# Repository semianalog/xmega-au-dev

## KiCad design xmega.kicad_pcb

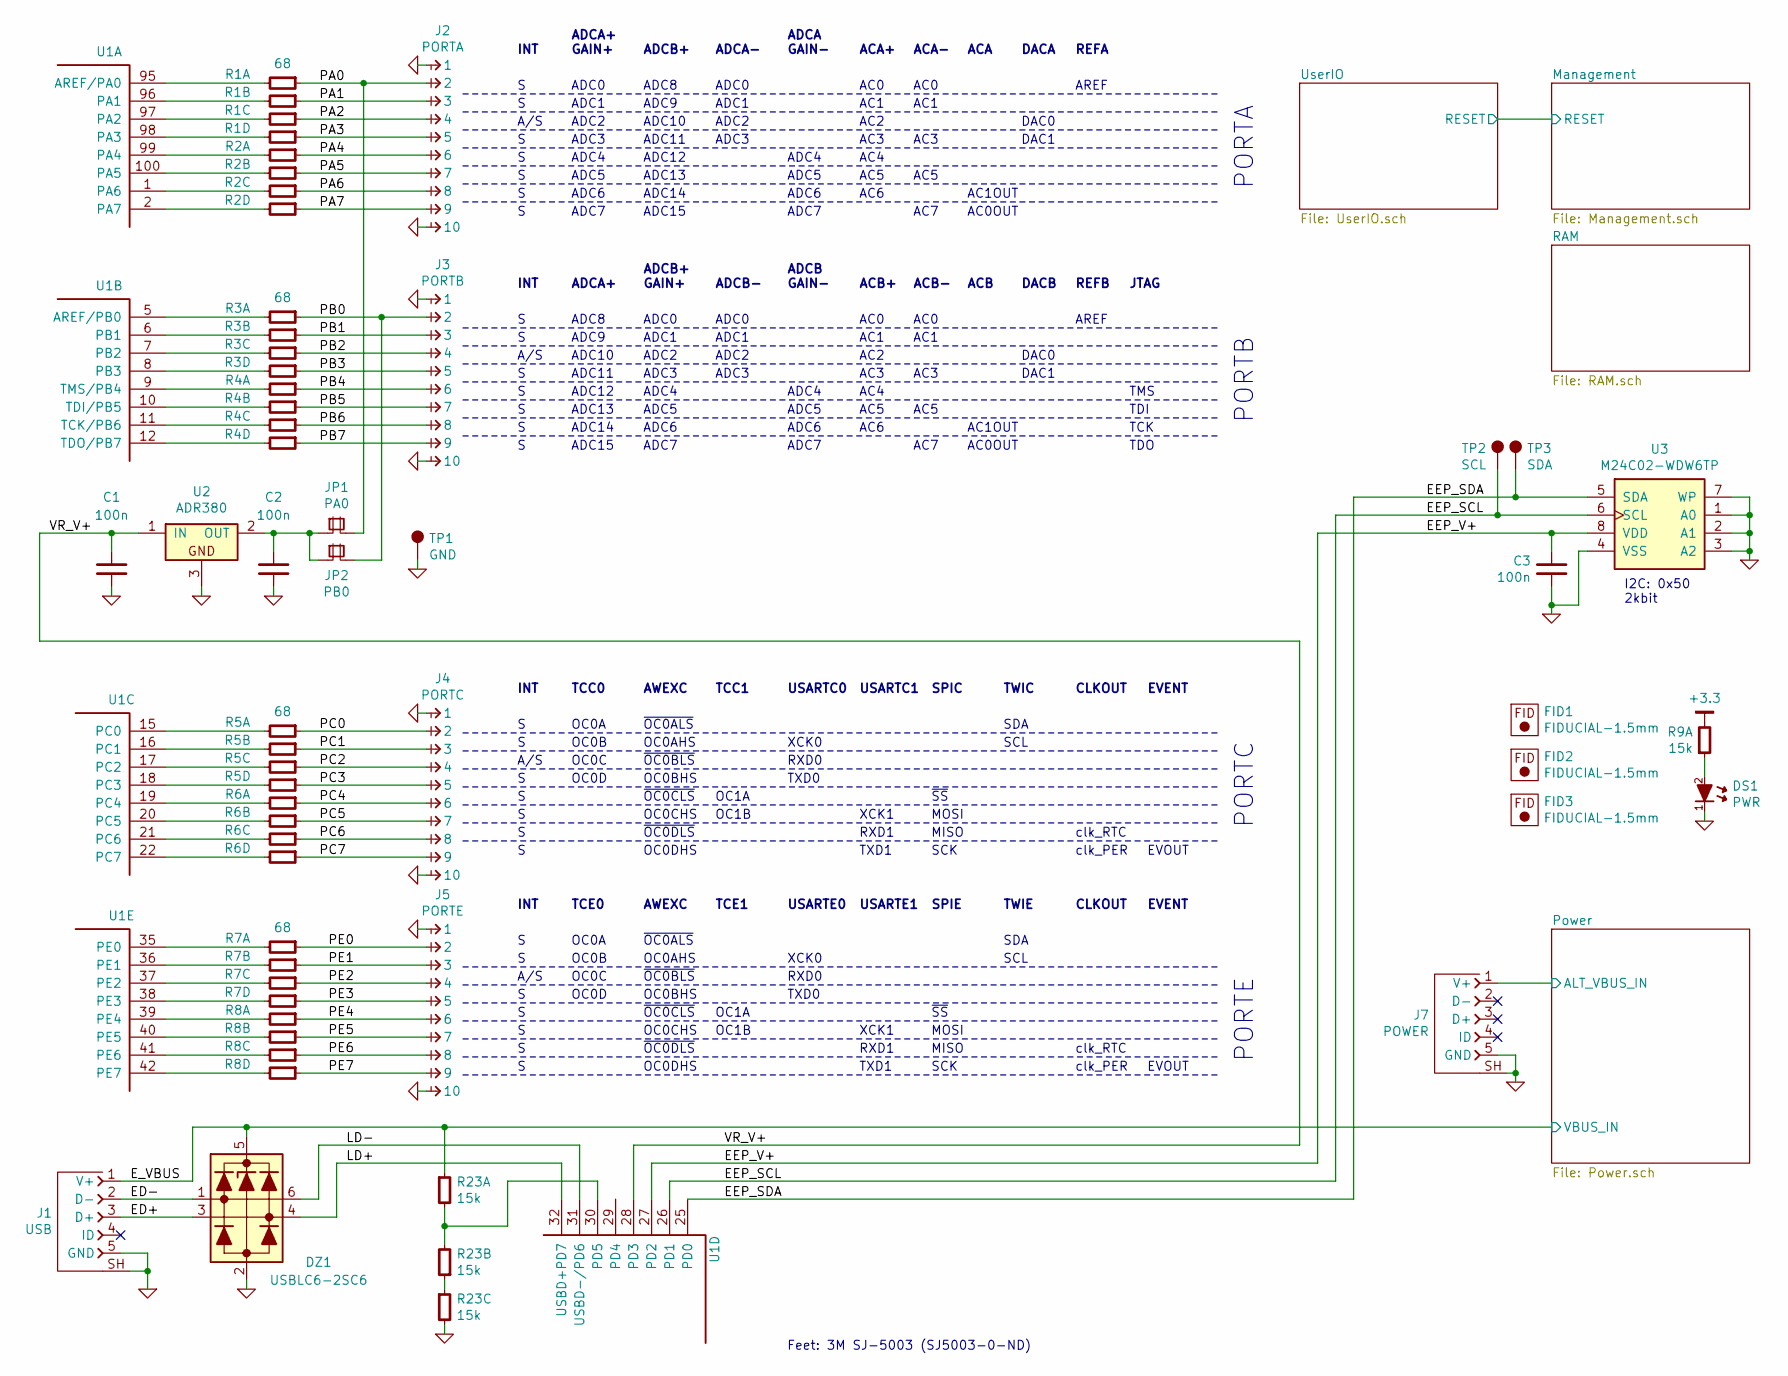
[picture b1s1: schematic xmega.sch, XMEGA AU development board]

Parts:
C1, C2, C3: 100n; CAPC1005X55
DS1: PWR; LED-0603
DZ1: USBLC6-2SC6; SOT-23-6
FID1, FID2, FID3: FIDUCIAL-1.5mm
J1: USB; CONN-10118194-0001LF-FCI
J2: PORTA; CONN-100MIL-M-1x10
J3: PORTB; CONN-100MIL-M-1x10
J4: PORTC; CONN-100MIL-M-1x10
J5: PORTE; CONN-100MIL-M-1x10
J7: POWER; CONN-10118194-0001LF-FCI
JP1: PA0; CONN-100MIL-M-1x2
JP2: PB0; CONN-100MIL-M-1x2
R1, R2, R3, R4, R5, R6, R7, R8: 68; RESCAXE80P160X320X70-8
R9, R23: 15k; RESCAXE80P160X320X70-8
TP1: GND; TESTPOINT-KEYSTONE-5018
TP2: SCL; TEST-SMD-SMALL
TP3: SDA; TEST-SMD-SMALL
U1: ATXMEGA128A1U-AU; QFP50P1600X1600X120-100
U2: ADR380; SOT-23
U3: M24C02-WDW6TP; SOP65P640X110-8

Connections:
+3.3: R9.8; also elsewhere on the board
/ED+: DZ1.3, J1.3 (D+)
/ED-: DZ1.1, J1.2 (D-)
/EEP_SCL: TP2.1, U1.26 (PD1), U3.6 (SCL)
/EEP_SDA: TP3.1, U1.25 (PD0), U3.5 (SDA)
/EEP_V+: C3.1, U1.27 (PD2), U3.8 (VDD)
/E_VBUS: DZ1.5, J1.1 (V+), R23.1; also elsewhere on the board
/LD+: DZ1.4, U1.32 (USBD+PD7)
/LD-: DZ1.6, U1.31 (USBD-/PD6)
/PA0: J2.2, JP1.2, R1.1
/PA1: J2.3, R1.2
/PA2: J2.4, R1.3
/PA3: J2.5, R1.4
/PA4: J2.6, R2.1
/PA5: J2.7, R2.2
/PA6: J2.8, R2.3
/PA7: J2.9, R2.4
/PB0: J3.2, JP2.2, R3.1
/PB1: J3.3, R3.2
/PB2: J3.4, R3.3
/PB3: J3.5, R3.4
/PB4: J3.6, R4.1
/PB5: J3.7, R4.2
/PB6: J3.8, R4.3
/PB7: J3.9, R4.4
/PC0: J4.2, R5.1
/PC1: J4.3, R5.2
/PC2: J4.4, R5.3
/PC3: J4.5, R5.4
/PC4: J4.6, R6.1
/PC5: J4.7, R6.2
/PC6: J4.8, R6.3
/PC7: J4.9, R6.4
/PE0: J5.2, R7.1
/PE1: J5.3, R7.2
/PE2: J5.4, R7.3
/PE3: J5.5, R7.4
/PE4: J5.6, R8.1
/PE5: J5.7, R8.2
/PE6: J5.8, R8.3
/PE7: J5.9, R8.4
/Power/ALT_VBUS_IN: J7.1 (V+); also elsewhere on the board
/VR_V+: C1.1, U1.28 (PD3), U2.1 (IN)
GND: C1.2, C2.2, C3.2, DS1.1 (K), DZ1.2, J1.5 (GND), J1.SH (SHIELD), J2.1, J2.10, J3.1, J3.10, J4.1, J4.10, J5.1, J5.10, J7.5 (GND), J7.SH (SHIELD), R23.6, TP1.1, U2.3, U3.1 (A0), U3.2 (A1), U3.3 (A2), U3.4 (VSS), U3.7 (WP); also elsewhere on the board
unnamed: C2.1, JP1.1, JP2.1, U2.2 (OUT)
unnamed: DS1.2 (A), R9.1
unnamed: R1.5, U1.98 (PA3)
unnamed: R1.6, U1.97 (PA2)
unnamed: R1.7, U1.96 (PA1)
unnamed: R1.8, U1.95 (AREF/PA0)
unnamed: R2.5, U1.2 (PA7)
unnamed: R2.6, U1.1 (PA6)
unnamed: R2.7, U1.100 (PA5)
unnamed: R2.8, U1.99 (PA4)
unnamed: R3.5, U1.8 (PB3)
unnamed: R3.6, U1.7 (PB2)
unnamed: R3.7, U1.6 (PB1)
unnamed: R3.8, U1.5 (AREF/PB0)
unnamed: R4.5, U1.12 (TDO/PB7)
unnamed: R4.6, U1.11 (TCK/PB6)
unnamed: R4.7, U1.10 (TDI/PB5)
unnamed: R4.8, U1.9 (TMS/PB4)
unnamed: R5.5, U1.18 (PC3)
unnamed: R5.6, U1.17 (PC2)
unnamed: R5.7, U1.16 (PC1)
unnamed: R5.8, U1.15 (PC0)
unnamed: R6.5, U1.22 (PC7)
unnamed: R6.6, U1.21 (PC6)
unnamed: R6.7, U1.20 (PC5)
unnamed: R6.8, U1.19 (PC4)
unnamed: R7.5, U1.38 (PE3)
unnamed: R7.6, U1.37 (PE2)
unnamed: R7.7, U1.36 (PE1)
unnamed: R7.8, U1.35 (PE0)
unnamed: R8.5, U1.42 (PE7)
unnamed: R8.6, U1.41 (PE6)
unnamed: R8.7, U1.40 (PE5)
unnamed: R8.8, U1.39 (PE4)
unnamed: R23.2, R23.3
unnamed: R23.7, R23.8, U1.30 (PD5)

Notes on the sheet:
I2C: 0x50 2kbit
Feet: 3M SJ-5003 (SJ5003-0-ND)
INT
A/S
TCC0
AWEXC
TCC1
USARTC0
USARTC1
SPIC
TWIC
CLKOUT
EVENT
OC0A
OC0B
OC0C
OC0D
~OC0ALS
OC0AHS
~OC0BLS
OC0BHS
~OC0CLS
OC0CHS
~OC0DLS
OC0DHS
OC1A
OC1B
XCK0
RXD0
TXD0
XCK1
RXD1
TXD1
SDA
SCL
~SS
MOSI
MISO
SCK
clk_RTC

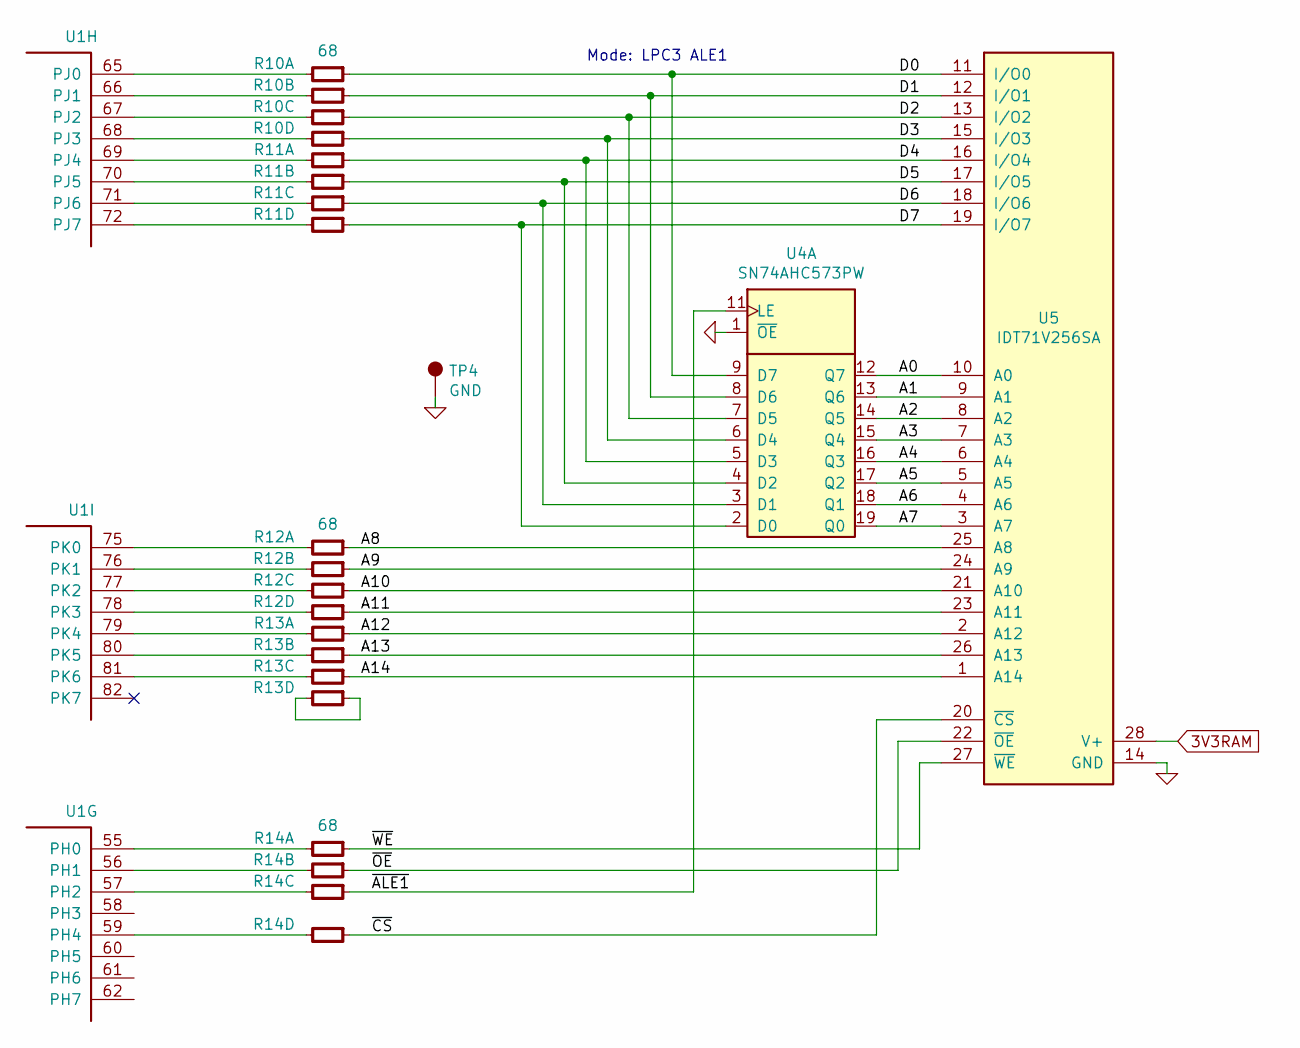
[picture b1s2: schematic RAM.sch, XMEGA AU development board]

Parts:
R10, R11, R12, R13, R14: 68; RESCAXE80P160X320X70-8
TP4: GND; TESTPOINT-KEYSTONE-5018
U1: ATXMEGA128A1U-AU; QFP50P1600X1600X120-100
U4: SN74AHC573PW; SOP65P640X110-20
U5: IDT71V256SA; SOJ127P1118X375-28

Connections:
3V3RAM: U5.28 (V+); also elsewhere on the board
/RAM/A0: U4.12 (Q7), U5.10 (A0)
/RAM/A1: U4.13 (Q6), U5.9 (A1)
/RAM/A2: U4.14 (Q5), U5.8 (A2)
/RAM/A3: U4.15 (Q4), U5.7 (A3)
/RAM/A4: U4.16 (Q3), U5.6 (A4)
/RAM/A5: U4.17 (Q2), U5.5 (A5)
/RAM/A6: U4.18 (Q1), U5.4 (A6)
/RAM/A7: U4.19 (Q0), U5.3 (A7)
/RAM/A8: R12.1, U5.25 (A8)
/RAM/A9: R12.2, U5.24 (A9)
/RAM/A10: R12.3, U5.21 (A10)
/RAM/A11: R12.4, U5.23 (A11)
/RAM/A12: R13.1, U5.2 (A12)
/RAM/A13: R13.2, U5.26 (A13)
/RAM/A14: R13.3, U5.1 (A14)
/RAM/D0: R10.1, U4.9 (D7), U5.11 (I/O0)
/RAM/D1: R10.2, U4.8 (D6), U5.12 (I/O1)
/RAM/D2: R10.3, U4.7 (D5), U5.13 (I/O2)
/RAM/D3: R10.4, U4.6 (D4), U5.15 (I/O3)
/RAM/D4: R11.1, U4.5 (D3), U5.16 (I/O4)
/RAM/D5: R11.2, U4.4 (D2), U5.17 (I/O5)
/RAM/D6: R11.3, U4.3 (D1), U5.18 (I/O6)
/RAM/D7: R11.4, U4.2 (D0), U5.19 (I/O7)
/RAM/~ALE1: R14.3, U4.11 (LE)
/RAM/~CS: R14.4, U5.20 (~CS)
/RAM/~OE: R14.2, U5.22 (~OE)
/RAM/~WE: R14.1, U5.27 (~WE)
GND: TP4.1, U4.1 (~OE), U5.14 (GND); also elsewhere on the board
unnamed: R10.5, U1.68 (PJ3)
unnamed: R10.6, U1.67 (PJ2)
unnamed: R10.7, U1.66 (PJ1)
unnamed: R10.8, U1.65 (PJ0)
unnamed: R11.5, U1.72 (PJ7)
unnamed: R11.6, U1.71 (PJ6)
unnamed: R11.7, U1.70 (PJ5)
unnamed: R11.8, U1.69 (PJ4)
unnamed: R12.5, U1.78 (PK3)
unnamed: R12.6, U1.77 (PK2)
unnamed: R12.7, U1.76 (PK1)
unnamed: R12.8, U1.75 (PK0)
unnamed: R13.4, R13.5
unnamed: R13.6, U1.81 (PK6)
unnamed: R13.7, U1.80 (PK5)
unnamed: R13.8, U1.79 (PK4)
unnamed: R14.5, U1.59 (PH4)
unnamed: R14.6, U1.57 (PH2)
unnamed: R14.7, U1.56 (PH1)
unnamed: R14.8, U1.55 (PH0)

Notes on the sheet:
Mode: LPC3 ALE1

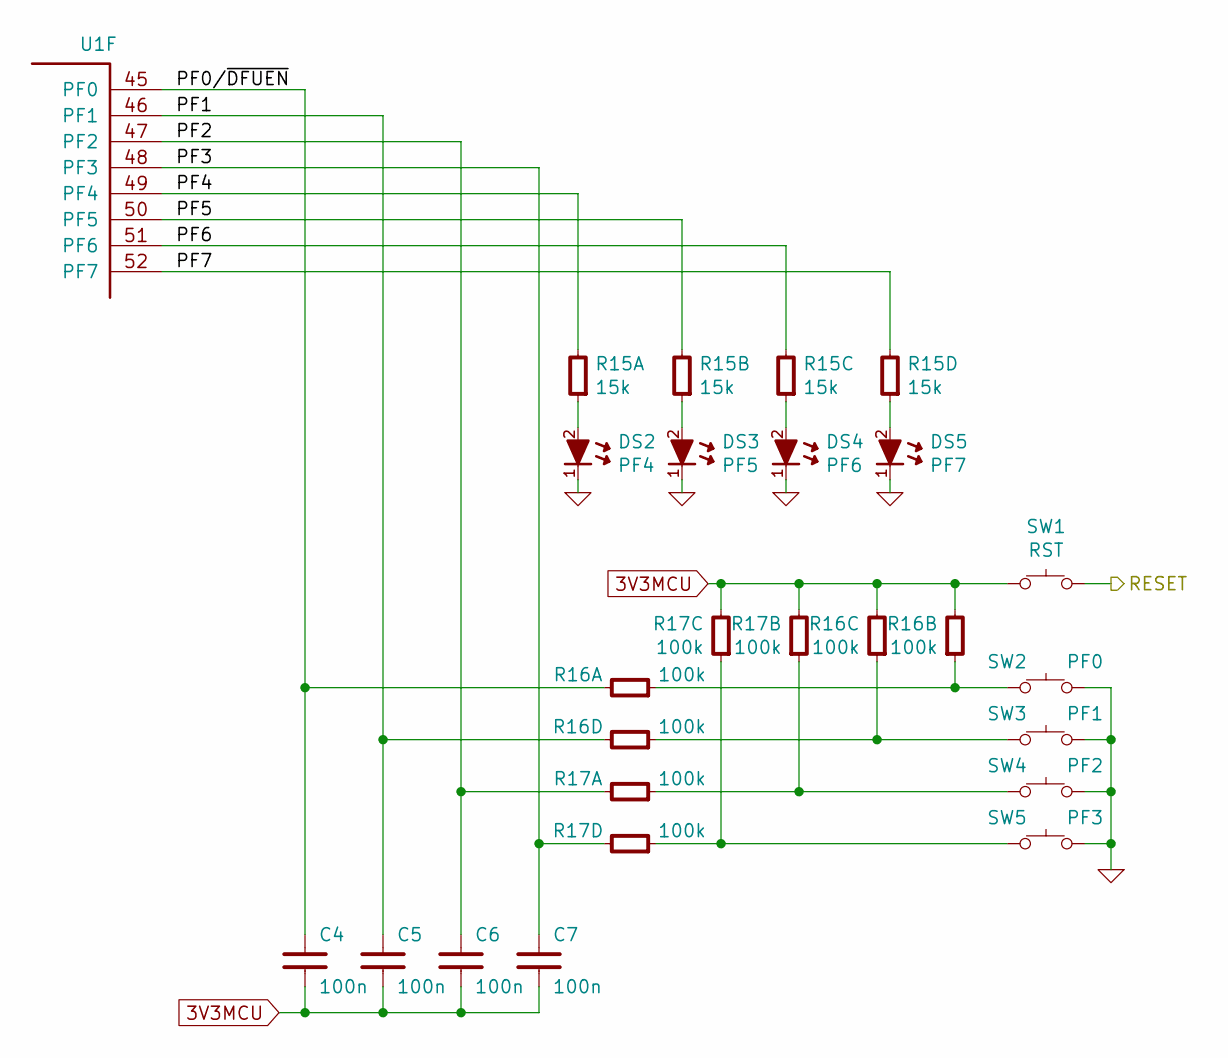
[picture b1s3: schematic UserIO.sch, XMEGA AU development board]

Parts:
C4, C5, C6, C7: 100n; CAPC1005X55
DS2: PF4; LED-0603
DS3: PF5; LED-0603
DS4: PF6; LED-0603
DS5: PF7; LED-0603
R15: 15k; RESCAXE80P160X320X70-8
R16, R17: 100k; RESCAXE80P160X320X70-8
SW1: RST; TE-FSMSM
SW2: PF0; TE-FSMSM
SW3: PF1; TE-FSMSM
SW4: PF2; TE-FSMSM
SW5: PF3; TE-FSMSM
U1: ATXMEGA128A1U-AU; QFP50P1600X1600X120-100

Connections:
3V3MCU: C4.2, C5.2, C6.2, C7.2, R16.6, R16.7, R17.6, R17.7, SW1.1; also elsewhere on the board
/Management/RESET: SW1.2; also elsewhere on the board
/UserIO/PF0/~DFUEN: C4.1, R16.8, U1.45 (PF0)
/UserIO/PF1: C5.1, R16.5, U1.46 (PF1)
/UserIO/PF2: C6.1, R17.8, U1.47 (PF2)
/UserIO/PF3: C7.1, R17.5, U1.48 (PF3)
/UserIO/PF4: R15.8, U1.49 (PF4)
/UserIO/PF5: R15.7, U1.50 (PF5)
/UserIO/PF6: R15.6, U1.51 (PF6)
/UserIO/PF7: R15.5, U1.52 (PF7)
GND: DS2.1 (K), DS3.1 (K), DS4.1 (K), DS5.1 (K), SW2.2, SW3.2, SW4.2, SW5.2; also elsewhere on the board
unnamed: DS2.2 (A), R15.1
unnamed: DS3.2 (A), R15.2
unnamed: DS4.2 (A), R15.3
unnamed: DS5.2 (A), R15.4
unnamed: R16.1, R16.2, SW2.1
unnamed: R16.3, R16.4, SW3.1
unnamed: R17.1, R17.2, SW4.1
unnamed: R17.3, R17.4, SW5.1

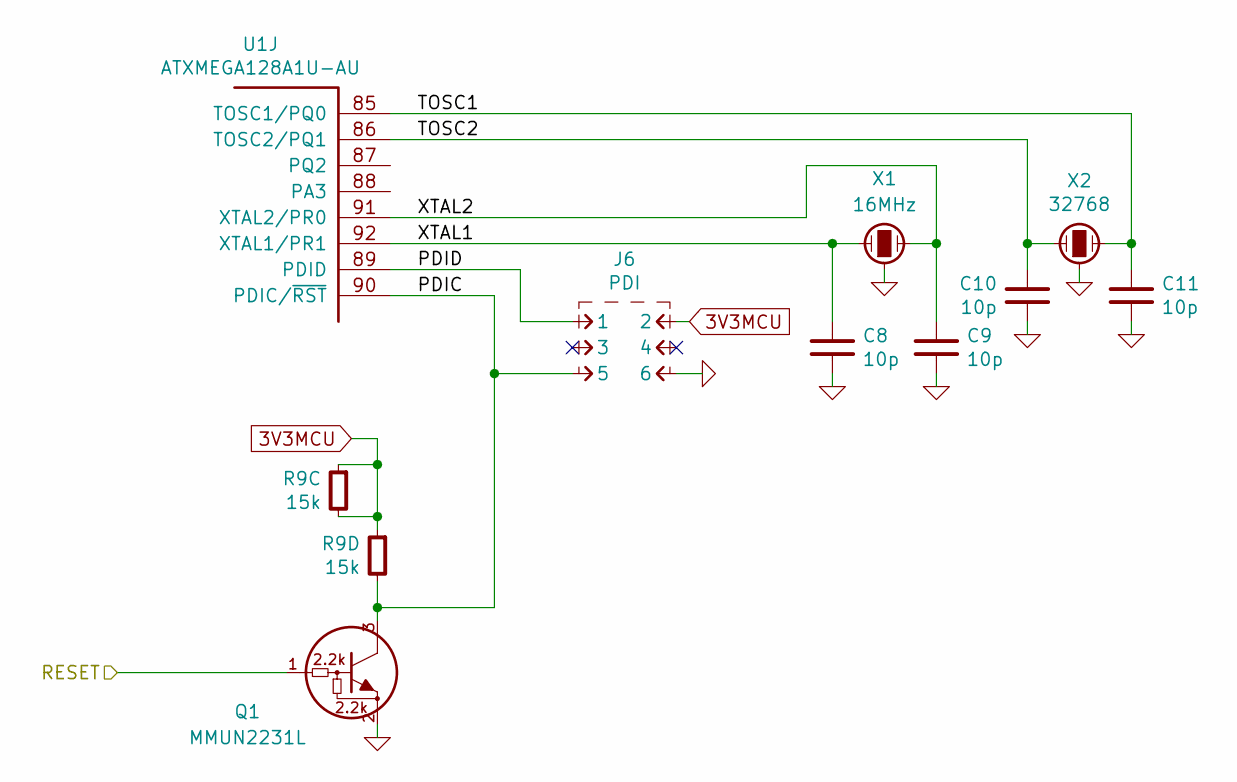
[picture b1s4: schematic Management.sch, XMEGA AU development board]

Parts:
C8, C9, C10, C11: 10p; CAPC1005X55
J6: PDI; CONN-100MIL-M-2x3-SHROUD
Q1: MMUN2231L; SOT-23
R9: 15k; RESCAXE80P160X320X70-8
U1: ATXMEGA128A1U-AU; QFP50P1600X1600X120-100
X1: 16MHz; ABRACON-ABM8G
X2: 32768

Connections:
3V3MCU: J6.2, R9.3, R9.4, R9.6; also elsewhere on the board
/Management/PDIC: J6.5, Q1.3 (C), R9.5, U1.90 (PDIC/~RST)
/Management/PDID: J6.1, U1.89 (PDID)
/Management/RESET: Q1.1 (B); also elsewhere on the board
/Management/TOSC1: C11.1, U1.85 (TOSC1/PQ0), X2.2
/Management/TOSC2: C10.1, U1.86 (TOSC2/PQ1), X2.1
/Management/XTAL1: C8.1, U1.92 (XTAL1/PR1), X1.1
/Management/XTAL2: C9.1, U1.91 (XTAL2/PR0), X1.2
GND: C8.2, C9.2, C10.2, C11.2, J6.6, Q1.2 (E), X1.3, X2.3; also elsewhere on the board

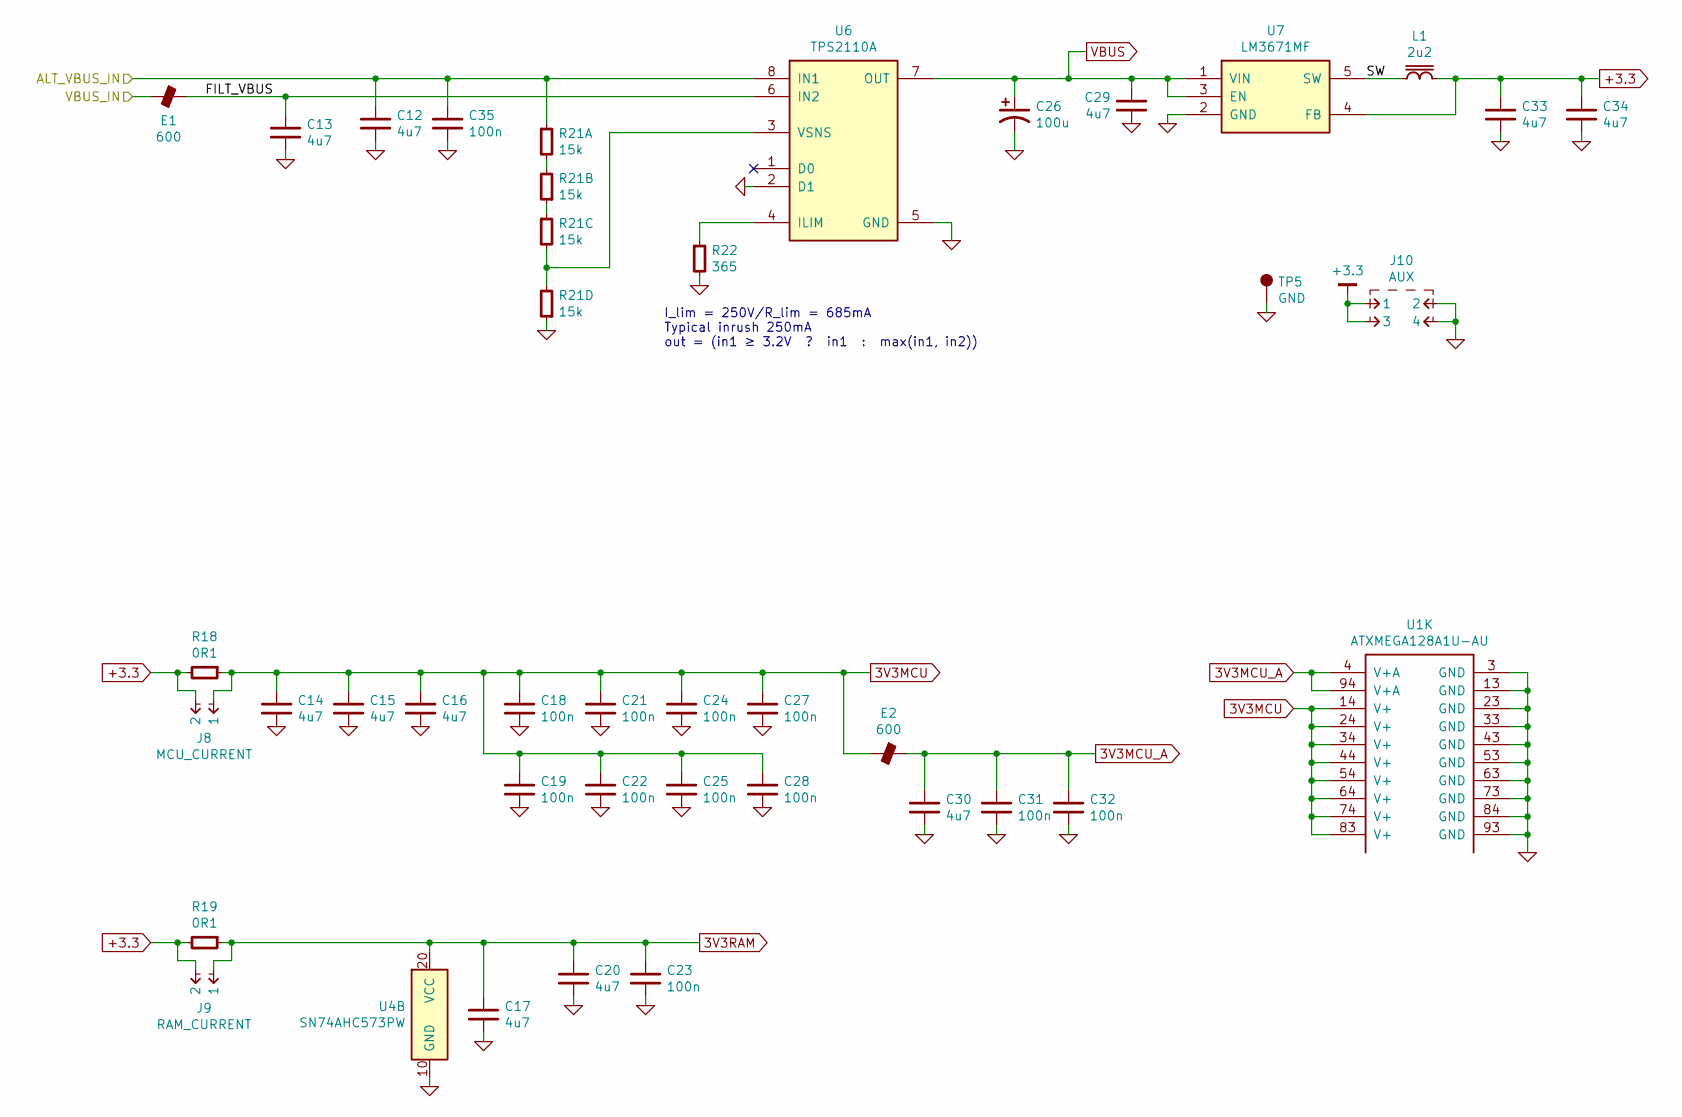
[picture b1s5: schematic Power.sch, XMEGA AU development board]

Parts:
C12, C13, C14, C15, C16, C17, C20, C29, C30, C33, C34: 4u7; CAPC1608X55
C18, C19, C21, C22, C23, C24, C25, C27, C28, C31, C32, C35: 100n; CAPC1005X55
C26: 100u; CAPAE530X540
E1, E2: 600; RESC3216X60
J8: MCU_CURRENT; CONN-100MIL-M-1x2
J9: RAM_CURRENT; CONN-100MIL-M-1x2
J10: AUX; CONN-100MIL-M-2x2
L1: 2u2; BOURNS-SRN3015
R18, R19: 0R1; RESC1608X50
R21: 15k; RESCAXE80P160X320X70-8
R22: 365; RESC1005X40
TP5: GND; TESTPOINT-KEYSTONE-5018
U1: ATXMEGA128A1U-AU; QFP50P1600X1600X120-100
U4: SN74AHC573PW; SOP65P640X110-20
U6: TPS2110A; SOP65P640X110-8
U7: LM3671MF; SOT-23-5

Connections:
3V3MCU: C14.1, C15.1, C16.1, C18.1, C19.1, C21.1, C22.1, C24.1, C25.1, C27.1, C28.1, E2.1, J8.1, R18.1, U1.14 (V+), U1.24 (V+), U1.34 (V+), U1.44 (V+), U1.54 (V+), U1.64 (V+), U1.74 (V+), U1.83 (V+); also elsewhere on the board
3V3MCU_A: C30.1, C31.1, C32.1, E2.2, U1.4 (V+A), U1.94 (V+A)
3V3RAM: C17.1, C20.1, C23.1, J9.1, R19.1, U4.20 (VCC); also elsewhere on the board
+3.3: C33.1, C34.1, J8.2, J9.2, J10.1, J10.3, L1.1, R18.2, R19.2, U7.4 (FB); also elsewhere on the board
/E_VBUS: E1.1; also elsewhere on the board
/Power/ALT_VBUS_IN: C12.2, C35.1, R21.1, U6.8 (IN1); also elsewhere on the board
/Power/FILT_VBUS: C13.2, E1.2, U6.6 (IN2)
/Power/SW: L1.2, U7.5 (SW)
GND: C12.1, C13.1, C14.2, C15.2, C16.2, C17.2, C18.2, C19.2, C20.2, C21.2, C22.2, C23.2, C24.2, C25.2, C26.2, C27.2, C28.2, C29.2, C30.2, C31.2, C32.2, C33.2, C34.2, C35.2, J10.2, J10.4, R21.4, R22.2, TP5.1, U1.3 (GND), U1.13 (GND), U1.23 (GND), U1.33 (GND), U1.43 (GND), U1.53 (GND), U1.63 (GND), U1.73 (GND), U1.84 (GND), U1.93 (GND), U4.10 (GND), U6.2 (D1), U6.5 (GND), U7.2 (GND); also elsewhere on the board
unnamed: R21.2, R21.3
unnamed: R21.5, R21.6, U6.3 (VSNS)
unnamed: R21.7, R21.8
unnamed: R22.1, U6.4 (ILIM)
VBUS: C26.1, C29.1, U6.7 (OUT), U7.1 (VIN), U7.3 (EN)

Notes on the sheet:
I_lim = 250V/R_lim = 685mA Typical inrush 250mA out = (in1 ≥ 3.2V ? in1 : max(in1, in2))

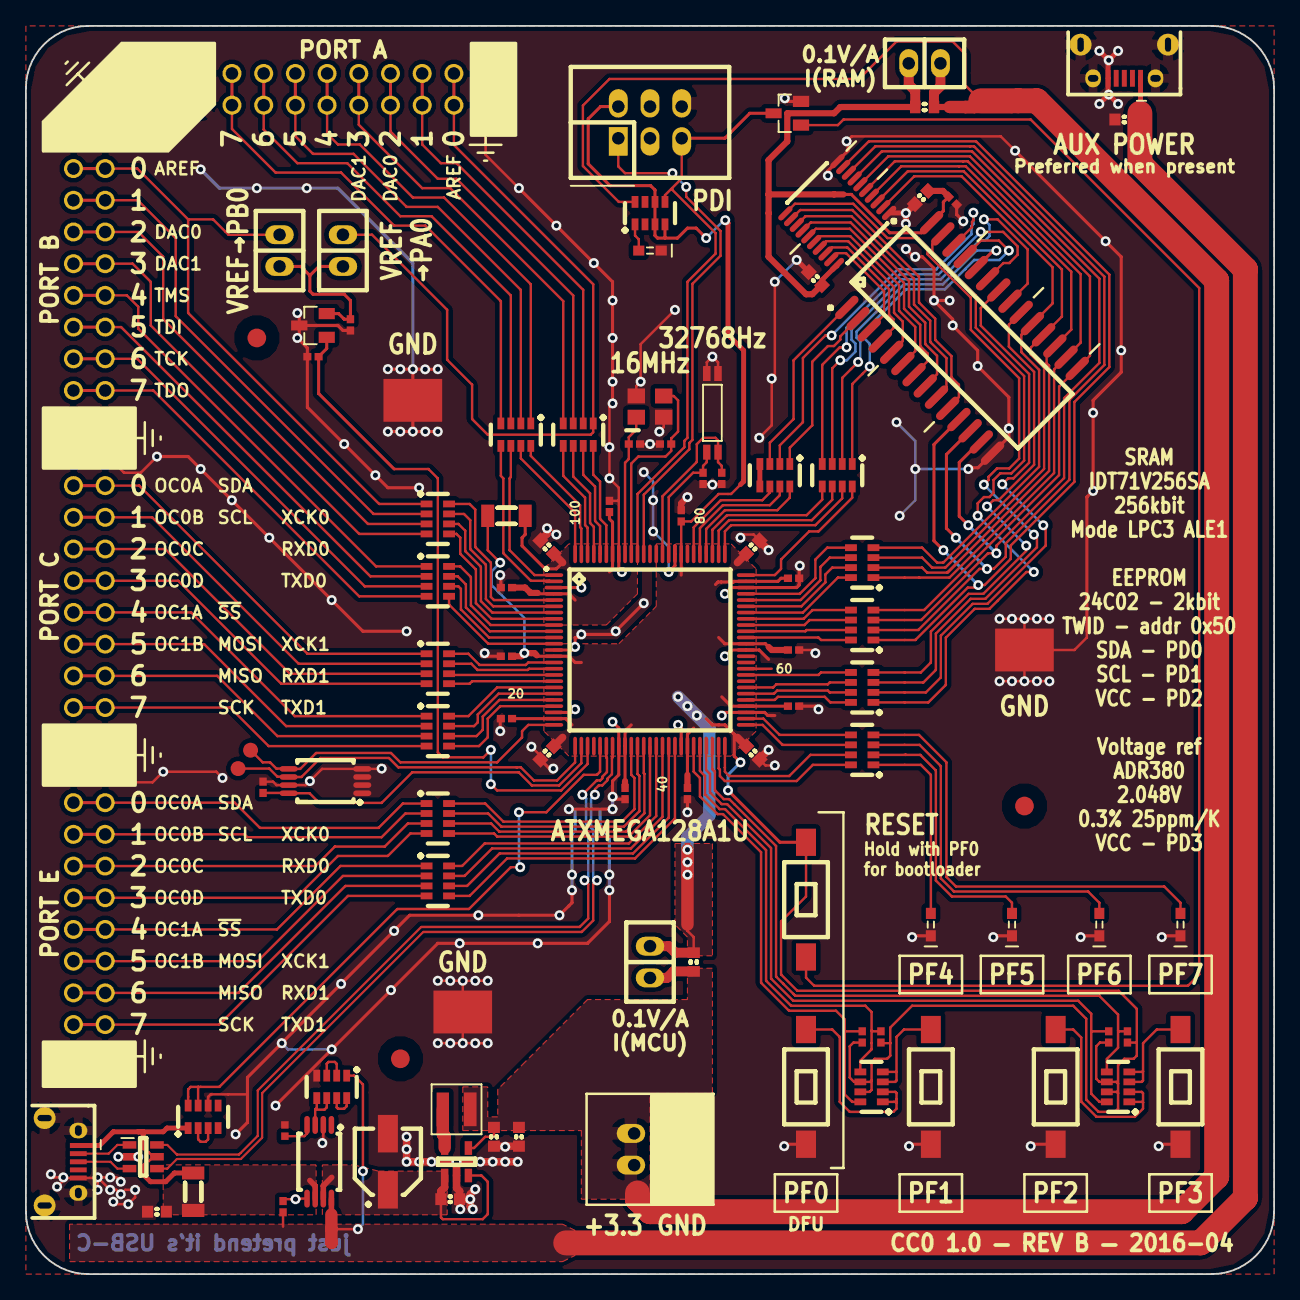
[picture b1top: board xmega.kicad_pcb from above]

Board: 2 copper layers, 100.0 x 100.0 mm, 101 parts (0 on the bottom side), 160 nets.

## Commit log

2016-03-22 Finished?
2016-03-22 Reannotate
2016-03-22 Update libraries
2016-03-22 Schematic tidy-ups and add VBUS sense
2016-03-22 Fix VBUS sense circuit
    Voltage delivered with 2x(3k3) divider was too low, switch to 3x(3k3)
2016-03-22 Rearrange Power schematic a bit
2016-03-22 Edit back silkscreen
2016-03-22 Final PCB adjustment, DRC, and gerber rendering
2016-03-22 Prepare BOM for ordering
2016-03-23 Adjust F.Fab layer as assembly diagram
2016-03-23 Add assembly diagram
2016-04-01 Bugfix: debounce causes bootloader entry on power
    Debounce capacitors were connected to ground, which held the IOs low at boot
    for about 20ms. Capacitors are now connected to 3.3V instead.
2016-04-01 Bugfix: crystal capacitance too high
2016-04-01 Decrease LED current
2016-04-01 Remove extra resistor R20
    With increase of R21 to 15k, it became insignificant - judged better
    to remove it and push the power switching threshold a bit lower than
    to add another BOM item to increase it.
2016-04-01 Decouple ALT_VBUS locally to U6
2016-04-01 Switch to passthrough USB TVS
2016-04-01 Decrease reset pullup
    Changing the LED resistors increased it
2016-04-01 Improved crystal layout
    Shorter traces, less coupling between RAM bus and TOSC
2016-04-01 R21: do not link pads under footprint - looks like shorts
2016-07-17 Add bootloader

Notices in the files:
Management.sch:
CC0: https://creativecommons.org/publicdomain/zero/1.0
xmega.kicad_pcb:
CC0 1.0 — REV B — 2016-04
